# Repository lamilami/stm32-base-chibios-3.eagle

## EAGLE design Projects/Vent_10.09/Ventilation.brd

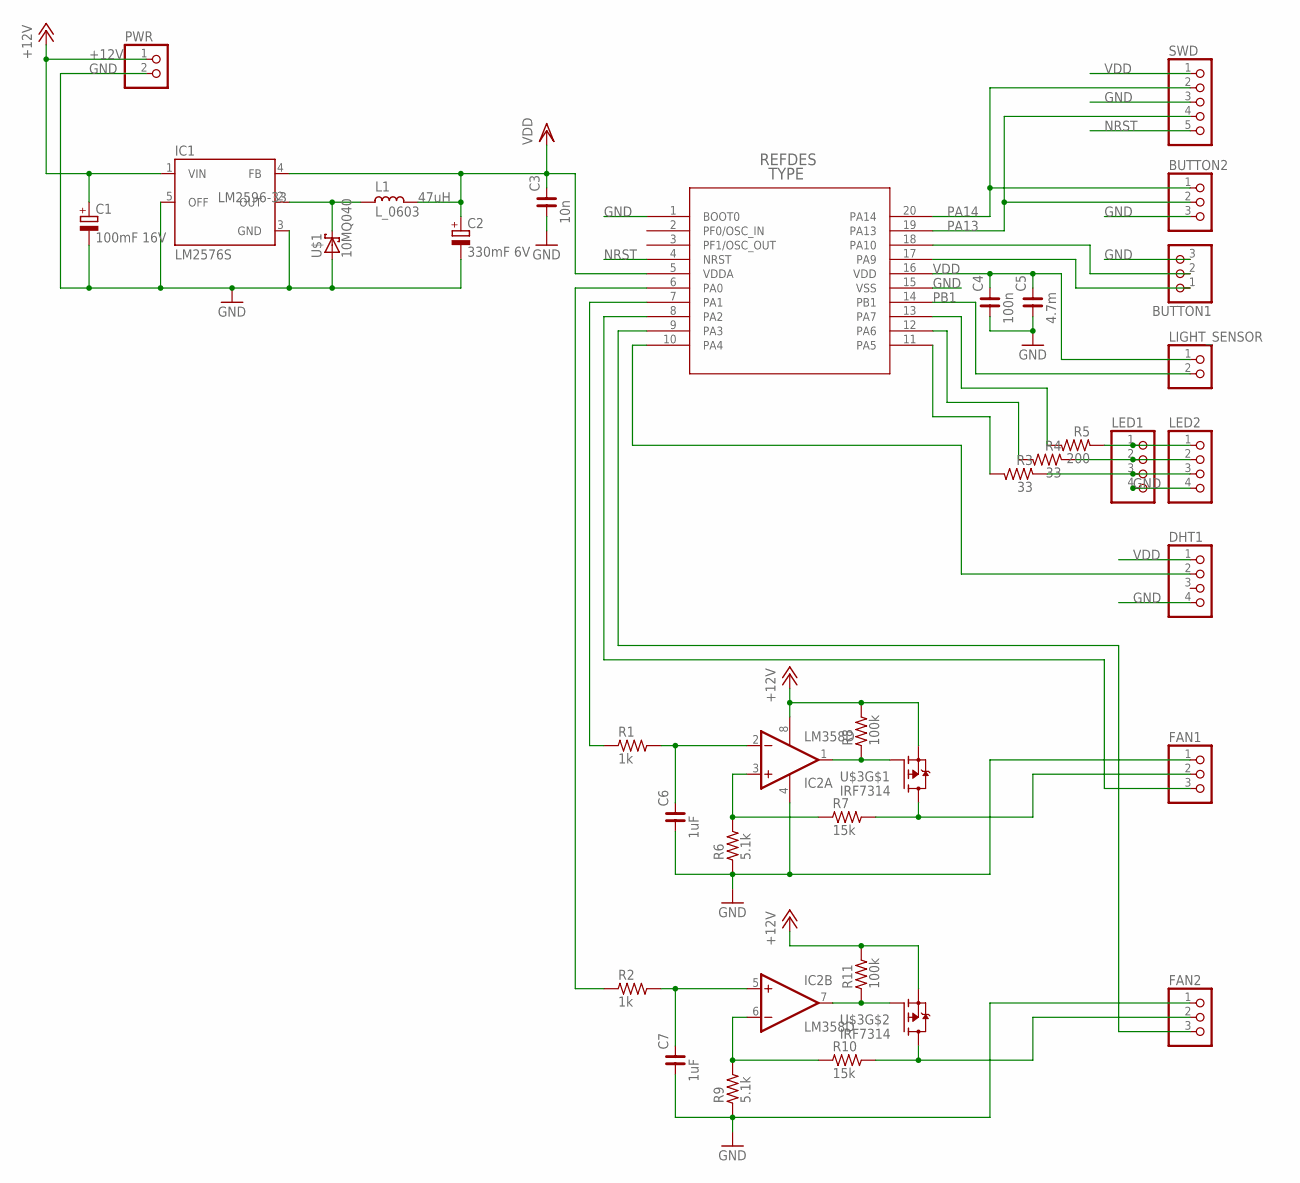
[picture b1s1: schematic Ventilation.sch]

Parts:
BUTTON1, BUTTON2: PINHD-1X03_2.54-S; 1X03-S
C1: 100mF 16V; SMC_D
C2: 330mF 6V; SMC_D
C3: 10n; C1206
C4: 100n; C1206
C5: 4.7m; C1206
C6, C7: 1uF; C0805
DHT1: PINHD-1X04_2.54-S; 1X04-S
FAN1, FAN2: PINHD-1X03_2.54-S; 1X03-S
IC1: LM2576S; TO263-5
IC2: LM358D; SO08
L1: L_0603; L0603
LED1, LED2: PINHD-1X04_2.54-S; 1X04-S
LIGHT_SENSOR: PINHD-1X02_2.54-S; 1X02-S
PWR: PINHD-1X02_2.54-S; 1X02-S
R1, R2: 1k; R0805
R3, R4: 33; R0805
R5: 200; R0805
R6, R9: 5.1k; R0805
R7, R10: 15k; R0805
R8, R11: 100k; R0805
SWD: PINHD-1X05_2.54-S; 1X05-S
U$1: 10MQ040; SMA
U$2: STM32F050F4P6; TSSOP20
U$3: IRF7314; SO-8

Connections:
+12V: C1.+, IC1.1 (VIN), IC2.8 (V+), PWR.1, R8.2, R11.2, U$3.1 (S), U$3.3 (S)
GND: BUTTON1.3, BUTTON2.3, C1.-, C2.-, C3.1, C4.1, C5.1, C6.1, C7.1, DHT1.4, FAN1.1, FAN2.1, IC1.3 (GND), IC1.5 (OFF), IC2.4 (V-), LED1.4, LED2.4, PWR.2, R6.1, R9.1, SWD.3, U$1.A, U$2.1 (BOOT0), U$2.15 (VSS)
unnamed: R1.1, U$2.7 (PA1)
unnamed: C6.2, IC2.2 (-IN), R1.2
unnamed: C7.2, IC2.5 (+IN), R2.2
unnamed: IC2.3 (+IN), R6.2, R7.1
unnamed: R2.1, U$2.6 (PA0)
unnamed: IC2.7 (OUT), R11.1, U$3.4 (G)
unnamed: LED1.1, LED2.1, R5.1
unnamed: FAN2.3, U$2.9 (PA3)
unnamed: FAN1.3, U$2.8 (PA2)
unnamed: DHT1.2, U$2.10 (PA4)
unnamed: IC1.2 (OUT), L1.2, U$1.C
unnamed: LED1.2, LED2.2, R4.1
unnamed: LED1.3, LED2.3, R3.1
unnamed: R5.2, U$2.13 (PA7)
unnamed: R4.2, U$2.12 (PA6)
unnamed: R3.2, U$2.11 (PA5)
unnamed: BUTTON1.1, U$2.17 (PA9)
unnamed: BUTTON1.2, U$2.18 (PA10)
unnamed: IC2.1 (OUT), R8.1, U$3.2 (G)
unnamed: FAN1.2, R7.2, U$3.7 (D), U$3.8 (D)
unnamed: FAN2.2, R10.2, U$3.5 (D), U$3.6 (D)
unnamed: IC2.6 (-IN), R9.2, R10.1
NRST: SWD.5, U$2.4 (NRST)
PA13: BUTTON2.2, SWD.4, U$2.19 (PA13)
PA14: BUTTON2.1, SWD.2, U$2.20 (PA14)
PB1: LIGHT_SENSOR.2, U$2.14 (PB1)
VDD: C2.+, C3.2, C4.2, C5.2, DHT1.1, IC1.4 (FB), L1.1, LIGHT_SENSOR.1, SWD.1, U$2.5 (VDDA), U$2.16 (VDD)

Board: 2 copper layers, 34 parts (0 on the bottom side), 29 nets, no tracks yet.

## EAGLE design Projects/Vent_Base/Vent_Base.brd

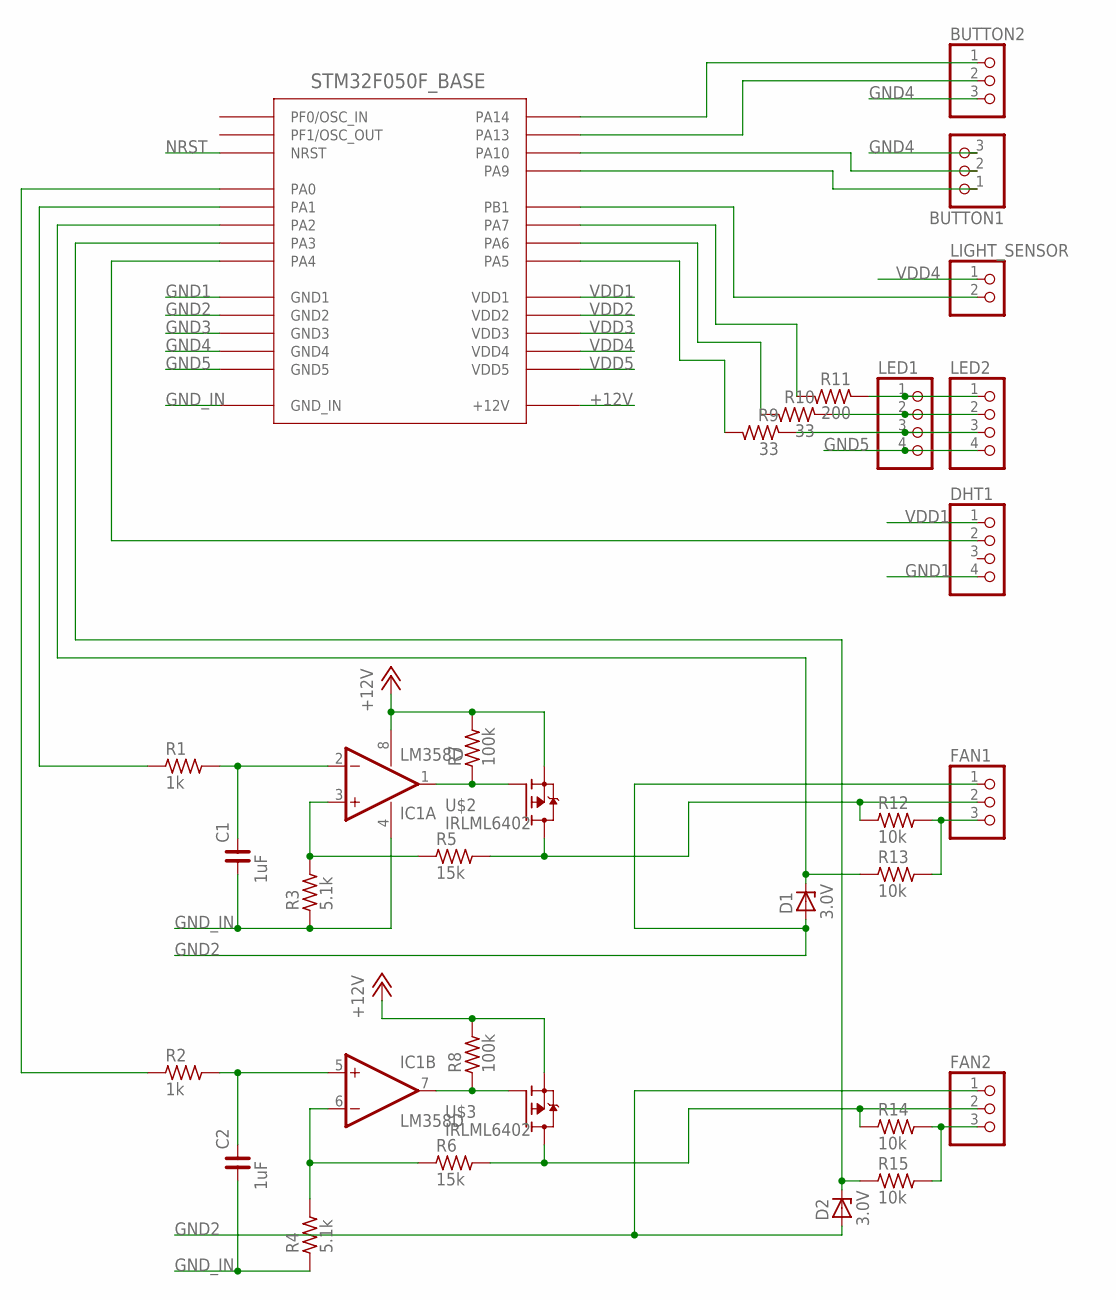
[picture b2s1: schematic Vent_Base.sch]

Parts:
BUTTON1, BUTTON2: PINHD-1X03_2.54-S; 1X03-S
C1, C2: 1uF; C0805
D1, D2: ZENER-DIODESOT23; SOT23
DHT1: PINHD-1X04_2.54-S; 1X04-S
FAN1, FAN2: PINHD-1X03_2.54-S; 1X03-S
IC1: LM358D; SO08
LED1, LED2: PINHD-1X04_2.54-S; 1X04-S
LIGHT_SENSOR: PINHD-1X02_2.54-S; 1X02-S
R1, R2: 1k; R1206
R3, R4: 5.1k; R1206
R5, R6: 15k; R1206
R7, R8: 100k; R1206
R9, R10: 33; R0805
R11: 200; R0805
R12, R13, R14, R15: 10k; R1206
U$1: STM32F050F_BASE_MOD; STM32_BASE_MOD
U$2, U$3: IRLML6402; SOT23

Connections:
+12V: IC1.8 (V+), R7.2, R8.2, U$1.+12V, U$2.2 (S), U$3.2 (S)
GND1: DHT1.4, U$1.GND1
GND2: D1.1 (A), D2.1 (A), FAN1.1, FAN2.1, U$1.GND2
GND3: U$1.GND3
GND4: BUTTON1.3, BUTTON2.3, U$1.GND4
GND5: LED1.4, LED2.4, U$1.GND5
GND_IN: C1.1, C2.1, IC1.4 (V-), R3.1, R4.1, U$1.GND_IN
unnamed: FAN2.3, R14.2, R15.2
unnamed: FAN1.3, R12.2, R13.2
unnamed: C1.2, IC1.2 (-IN), R1.2
unnamed: C2.2, IC1.5 (+IN), R2.2
unnamed: IC1.7 (OUT), R8.1, U$3.1 (G)
unnamed: LED1.1, LED2.1, R11.1
unnamed: IC1.3 (+IN), R3.2, R5.1
unnamed: LED1.2, LED2.2, R10.1
unnamed: LED1.3, LED2.3, R9.1
unnamed: IC1.1 (OUT), R7.1, U$2.1 (G)
unnamed: FAN1.2, R5.2, R12.1, U$2.3 (D)
unnamed: FAN2.2, R6.2, R14.1, U$3.3 (D)
unnamed: IC1.6 (-IN), R4.2, R6.1
NRST: U$1.NRST
PA0: R2.1, U$1.PA0
PA1: R1.1, U$1.PA1
PA2: D1.3 (C), R13.1, U$1.PA2
PA3: D2.3 (C), R15.1, U$1.PA3
PA4: DHT1.2, U$1.PA4
PA5: R9.2, U$1.PA5
PA6: R10.2, U$1.PA6
PA7: R11.2, U$1.PA7
PA9: BUTTON1.1, U$1.PA9
PA10: BUTTON1.2, U$1.PA10
PA13: BUTTON2.2, U$1.PA13
PA14: BUTTON2.1, U$1.PA14
PB1: LIGHT_SENSOR.2, U$1.PB1
VDD1: DHT1.1, U$1.VDD1
VDD2: U$1.VDD2
VDD3: U$1.VDD3
VDD4: LIGHT_SENSOR.1, U$1.VDD4
VDD5: U$1.VDD5

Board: 2 copper layers, 31 parts (0 on the bottom side), 34 nets, no tracks yet.

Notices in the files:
parts and their libraries:
rc-master-smd: Copyright (C) 2007, Bob Starr
SparkFun-PowerIC: Licensing: CC v3.0 Share-Alike You are welcome to use this library for commercial purposes.
